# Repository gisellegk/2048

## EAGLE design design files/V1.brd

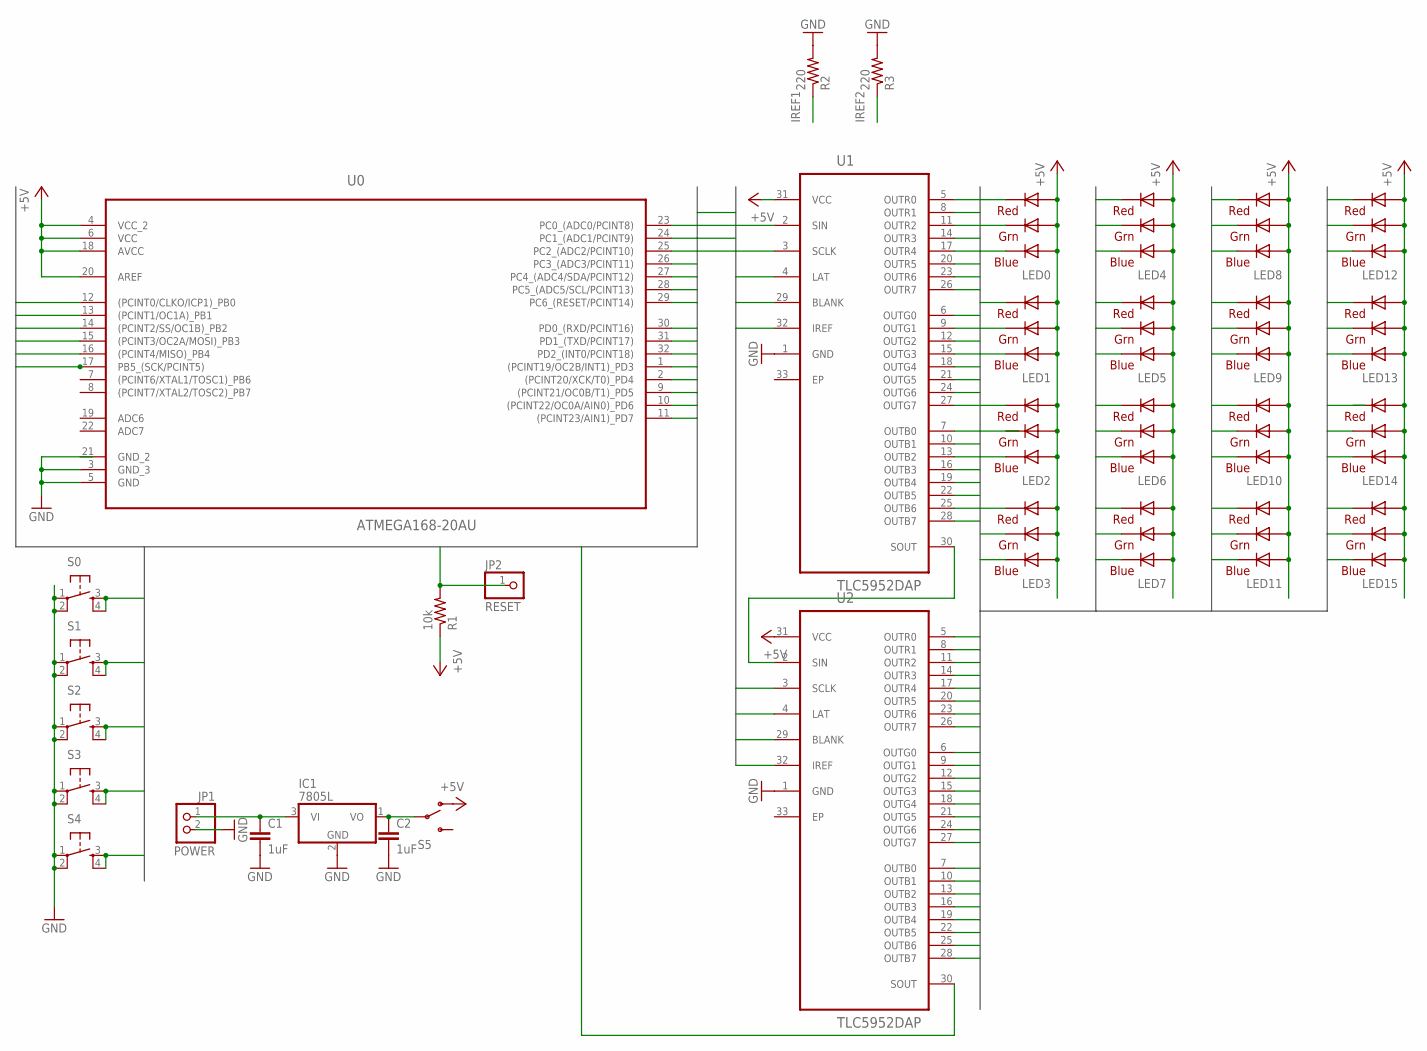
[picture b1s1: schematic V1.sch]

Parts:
C1, C2: 1uF; C2.5-3
IC1: 7805L; TO92
JP1: POWER; 1X02
JP2: RESET; 1X01
LED0, LED1, LED2, LED3, LED4, LED5, LED6, LED7, LED8, LED9, LED10, LED11, LED12, LED13, LED14, LED15: RGBLED5050
R1: 10k; 0207/10
R2, R3: 220; 0207/10
S0, S1, S2, S3, S4: TAC_SWITCHPTH; TACTILE-PTH
S5: SWITCH-SPDTPTH; SWITCH-SPDT
U0: ATMEGA168-20AU; QFP80P900X900X120-32N
U1, U2: TLC5952DAP; SOP65P810X120-33N

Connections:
+5V: LED0.1 (GREEN_A), LED0.2 (RED_A), LED0.3 (BLUE_A), LED1.1 (GREEN_A), LED1.2 (RED_A), LED1.3 (BLUE_A), LED2.1 (GREEN_A), LED2.2 (RED_A), LED2.3 (BLUE_A), LED3.1 (GREEN_A), LED3.2 (RED_A), LED3.3 (BLUE_A), LED4.1 (GREEN_A), LED4.2 (RED_A), LED4.3 (BLUE_A), LED5.1 (GREEN_A), LED5.2 (RED_A), LED5.3 (BLUE_A), LED6.1 (GREEN_A), LED6.2 (RED_A), LED6.3 (BLUE_A), LED7.1 (GREEN_A), LED7.2 (RED_A), LED7.3 (BLUE_A), LED8.1 (GREEN_A), LED8.2 (RED_A), LED8.3 (BLUE_A), LED9.1 (GREEN_A), LED9.2 (RED_A), LED9.3 (BLUE_A), LED10.1 (GREEN_A), LED10.2 (RED_A), LED10.3 (BLUE_A), LED11.1 (GREEN_A), LED11.2 (RED_A), LED11.3 (BLUE_A), LED12.1 (GREEN_A), LED12.2 (RED_A), LED12.3 (BLUE_A), LED13.1 (GREEN_A), LED13.2 (RED_A), LED13.3 (BLUE_A), LED14.1 (GREEN_A), LED14.2 (RED_A), LED14.3 (BLUE_A), LED15.1 (GREEN_A), LED15.2 (RED_A), LED15.3 (BLUE_A), R1.1, S5.1 (O), U0.4 (VCC_2), U0.6 (VCC), U0.18 (AVCC), U0.20 (AREF), U1.31 (VCC), U2.31 (VCC)
ANALOG0: U0.23 (PC0_(ADC0/PCINT8))
ANALOG1: U0.24 (PC1_(ADC1/PCINT9))
ANALOG2: U0.25 (PC2_(ADC2/PCINT10))
ANALOG3: U0.26 (PC3_(ADC3/PCINT11))
ANALOG4: U0.27 (PC4_(ADC4/SDA/PCINT12))
ANALOG5: U0.28 (PC5_(ADC5/SCL/PCINT13))
CARRY: U1.30 (SOUT), U2.2 (SIN)
DIGITAL0: U0.30 (PD0_(RXD/PCINT16))
DIGITAL1: U0.31 (PD1_(TXD/PCINT17))
DIGITAL2: S1.3, S1.4, U0.32 (PD2_(INT0/PCINT18))
DIGITAL3: U0.1 ((PCINT19/OC2B/INT1)_PD3), U1.2 (SIN)
DIGITAL4: S2.3, S2.4, U0.2 ((PCINT20/XCK/T0)_PD4)
DIGITAL5: U0.9 ((PCINT21/OC0B/T1)_PD5), U1.3 (SCLK), U2.3 (SCLK)
DIGITAL6: U0.10 ((PCINT22/OC0A/AIN0)_PD6), U1.4 (LAT), U2.4 (LAT)
DIGITAL7: S3.3, S3.4, U0.11 ((PCINT23/AIN1)_PD7)
DIGITAL8: S4.3, S4.4, U0.12 ((PCINT0/CLKO/ICP1)_PB0)
DIGITAL9: U0.13 ((PCINT1/OC1A)_PB1), U1.29 (BLANK), U2.29 (BLANK)
DIGITAL10: U0.14 ((PCINT2/SS/OC1B)_PB2), U2.30 (SOUT)
DIGITAL11: U0.15 ((PCINT3/OC2A/MOSI)_PB3)
DIGITAL12: S0.3, S0.4, U0.16 ((PCINT4/MISO)_PB4)
DIGITAL13: U0.17 (PB5_(SCK/PCINT5))
GND: C1.2, C2.2, IC1.2 (GND), JP1.2, R2.2, R3.2, S0.1, S0.2, S1.1, S1.2, S2.1, S2.2, S3.1, S3.2, S4.1, S4.2, U0.3 (GND_3), U0.5 (GND), U1.1 (GND), U2.1 (GND)
IREF1: R2.1, U1.32 (IREF)
IREF2: R3.1, U2.32 (IREF)
unnamed: C2.1, IC1.1 (VO), S5.2
unnamed: C1.1, IC1.3 (VI), JP1.1
OUTB0: LED0.4 (BLUE_C), U1.7 (OUTB0)
OUTB1: LED1.4 (BLUE_C), U1.10 (OUTB1)
OUTB2: LED2.4 (BLUE_C), U1.13 (OUTB2)
OUTB3: LED3.4 (BLUE_C), U1.16 (OUTB3)
OUTB4: LED4.4 (BLUE_C), U1.19 (OUTB4)
OUTB5: LED5.4 (BLUE_C), U1.22 (OUTB5)
OUTB6: LED6.4 (BLUE_C), U1.25 (OUTB6)
OUTB7: LED7.4 (BLUE_C), U1.28 (OUTB7)
OUTB8: LED8.4 (BLUE_C), U2.7 (OUTB0)
OUTB9: LED9.4 (BLUE_C), U2.10 (OUTB1)
OUTB10: LED10.4 (BLUE_C), U2.13 (OUTB2)
OUTB11: LED11.4 (BLUE_C), U2.16 (OUTB3)
OUTB12: LED12.4 (BLUE_C), U2.19 (OUTB4)
OUTB13: LED13.4 (BLUE_C), U2.22 (OUTB5)
OUTB14: LED14.4 (BLUE_C), U2.25 (OUTB6)
OUTB15: LED15.4 (BLUE_C), U2.28 (OUTB7)
OUTG0: LED0.6 (GREEN_C), U1.6 (OUTG0)
OUTG1: LED1.6 (GREEN_C), U1.9 (OUTG1)
OUTG2: U1.12 (OUTG2)
OUTG3: LED3.6 (GREEN_C), U1.15 (OUTG3)
OUTG4: LED4.6 (GREEN_C), U1.18 (OUTG4)
OUTG5: LED5.6 (GREEN_C), U1.21 (OUTG5)
OUTG6: LED6.6 (GREEN_C), U1.24 (OUTG6)
OUTG7: LED7.6 (GREEN_C), U1.27 (OUTG7)
OUTG8: LED8.6 (GREEN_C), U2.6 (OUTG0)
OUTG9: LED9.6 (GREEN_C), U2.9 (OUTG1)
OUTG10: LED10.6 (GREEN_C), U2.12 (OUTG2)
OUTG11: LED11.6 (GREEN_C), U2.15 (OUTG3)
OUTG12: LED12.6 (GREEN_C), U2.18 (OUTG4)
OUTG13: LED13.6 (GREEN_C), U2.21 (OUTG5)
OUTG14: LED14.6 (GREEN_C), U2.24 (OUTG6)
OUTG15: LED15.6 (GREEN_C), U2.27 (OUTG7)
OUTR0: LED0.5 (RED_C), U1.5 (OUTR0)
OUTR1: LED1.5 (RED_C), U1.8 (OUTR1)
OUTR2: LED2.5 (RED_C), U1.11 (OUTR2)
OUTR3: LED3.5 (RED_C), U1.14 (OUTR3)
OUTR4: LED4.5 (RED_C), U1.17 (OUTR4)
OUTR5: LED5.5 (RED_C), U1.20 (OUTR5)
OUTR6: LED6.5 (RED_C), U1.23 (OUTR6)
OUTR7: LED7.5 (RED_C), U1.26 (OUTR7)
OUTR8: LED8.5 (RED_C), U2.5 (OUTR0)
OUTR9: LED9.5 (RED_C), U2.8 (OUTR1)
OUTR10: LED10.5 (RED_C), U2.11 (OUTR2)
OUTR11: LED11.5 (RED_C), U2.14 (OUTR3)
OUTR12: LED12.5 (RED_C), U2.17 (OUTR4)
OUTR13: LED13.5 (RED_C), U2.20 (OUTR5)
OUTR14: U2.23 (OUTR6)
OUTR15: LED15.5 (RED_C), U2.26 (OUTR7)
RESET: JP2.1, R1.2, U0.29 (PC6_(RESET/PCINT14))

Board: 2 copper layers, 33 parts (4 on the bottom side), 64 nets, no tracks yet.

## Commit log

2014-08-26 adding design files and test cpp file
2014-10-12 add block object and 2048 main file. also hello world was apparently modified.

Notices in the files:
parts and their libraries:
SparkFun-Electromechanical: Licensing: Creative Commons ShareAlike 4.0 International - https://creativecommons.org/licenses/by-sa/4.0
